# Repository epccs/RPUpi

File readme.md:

# RPUpi

From <https://github.com/epccs/RPUpi>

## Overview

Shield used to connect a Raspberry Pi Zero (or W) to serial that can be shared (multidrop). The targets presently available are [RPUno], [RPUlux], and [Irrigate7]. The hardware allows the bus to be controlled so the host sees a single target (for bootload) or any number of them.  

A [RPUadpt] shield is also available if the host SBC does not use the Raspberry Pi 40 pin header.

[RPUno]: https://github.com/epccs/RPUno
[RPUlux]: https://github.com/epccs/RPUlux
[Irrigate7]: https://github.com/epccs/Irrigate7
[RPUadpt]: https://github.com/epccs/RPUadpt
[RPUftdi]: https://github.com/epccs/RPUftdi

## Status

[Options](./Hardware#bill-of-materials)

## [Hardware](./Hardware)

Hardware files include schematic and board images, bill of materials, and my notes on testing, evaluation, and schooling.

## Example

Both the SBC and microcontroller(s) can run simple UART serial communication software (e.g. all the RS232 software I have tried seems to work). I prefer textual commands, so my examples generally use a textual command processor which echoes back the command like an interactive terminal, the commands are used by the firmware command processor to run routines or configure state machines on the bare metal microcontrollers. The SBC host the toolchain so it can compile the firmware from the source which can be managed with git (e.g. GitHub, GitLab...) or anyway the user wishes. The toolchains uploader can be used to send the firmware to the targets bootloader. The result is one or more bare metal targets can receive updates that are compiled from source without the need for a bare metal network stack. This is not an IoT system, it is a computer hosting an operating system and toolchain connected with physical wires to bare metal embedded controllers. It is also not dependent on any cloud-based services.

To bootload the AVR from the Raspberry Pi hardware serial port it needs to be enabled for [serial] so Linux can use the port, also the [RTS and CTS] pin functions should be enabled since nRTS is used to start the bootloader (in place of the nDTR trick used by an Arduino Uno). 

[serial]: ./Hardware/Testing/linux.md#serial
[RTS and CTS]: ./RPiRtsCts

The Pi Zero also needs a way to [halt] from a push button. When the RPUpi shield is mounted on a target board (e.g. [RPUno]) the VIN pin can be powered off with a [power management] technique.  This allows a manual shutdown and for the local target to request a halt using an I2C command. It should help with redundancy techniques, so two or more SBC's with [failover] can ensure data from the targets keep flowing. 

[failover]: https://en.wikipedia.org/wiki/Failover
[halt]: ./Shutdown
[power management]: https://github.com/epccs/RPUno/tree/master/PwrMgt

## AVR toolchain

The core files for this boards bus manager are in the /lib folder. Each example has its files and a Makefile in its own folder. The toolchain packages that I use are available on Ubuntu and Raspbian. 

```
sudo apt-get install git make gcc-avr binutils-avr gdb-avr avr-libc avrdude
git clone https://github.com/epccs/RPUpi
```

* [gcc-avr](https://packages.ubuntu.com/search?keywords=gcc-avr)
* [binutils-avr](https://packages.ubuntu.com/search?keywords=binutils-avr)
* [gdb-avr](https://packages.ubuntu.com/search?keywords=gdb-avr)
* [avr-libc](https://packages.ubuntu.com/search?keywords=avr-libc)
* [avrdude](https://packages.ubuntu.com/search?keywords=avrdude)

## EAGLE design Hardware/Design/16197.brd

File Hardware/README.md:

# Hardware

## Overview

This board connects a Pi Zero [W] to a multi-drop serial bus and a control board with a target (e.g. [RPUno], [RPUlux], [RPUicp], [Irrigate7]). 

[RPUno]: https://github.com/epccs/RPUno
[RPUlux]: https://github.com/epccs/RPUlux
[RPUicp]: https://github.com/epccs/RPUicp
[Irrigate7]: https://github.com/epccs/Irrigate7

## Inputs/Outputs/Functions

```
        Pi Zero power is from a 5V SMPS regulator powered by the Vin pin
        Pi Zero UART connects crossover style to the rpubus pairs
        rpubus pairs daisy-chain to other RPUpi or RPUadpt shields
        The UART's from multiple targets may connect to the rpubus pairs 
        An out of band management pair is used to control host to target (P2P) connection.
        SPI is available between SBC and the local target.
```

## Uses

```
        Raspberry Pi with a Raspian Linux instance is a compelling platform.
        Accessing the machine instance with SSH is prefered.
        Serving files with Samba is availalbe, but not prefered.
        The machine instance has a physical serial link (rpubus ) to the bare metal targets.
```

## Notice

```
        If the Pi Zero bootloads its local board (the one under the RPUpi) then 
        the VIN power from the local board must not turn off after a reset 
        (the defaut setup has been tested and works). 
 ```

# Table Of Contents

1. [Status](#status)
2. [Design](#design)
3. [Bill of Materials](#bill-of-materials)
4. [How To Use](#how-to-use)

# Status

```
        ^5  Done: Design, Layout, BOM, Review*, Order Boards, Assembly, Testing,
            WIP: Evaluation.
            Todo: 
            *during review the Design may change without changing the revision.
            AVR's nSS should goto R-Pi's nCE00 not nCE10.

        ^4  Done: Design, Layout, BOM, Review*, Order Boards, Assembly, Testing,
            WIP: Evaluation.
            Todo: 
            *during review the Design may change without changing the revision.
            IOREF is for I2C and UART
            SPI_IOREF is for SPI only
            Add SPI nSS so the Raspery Pi CE10 can use it, (it was tested with RPUadpt^6)
            remove ADC6 and ADC7.
            remove smd mounts for 100 Ohm pair termination.
            Use TI's 5V THVD1500, wich cost less and has better specs.
            Run Manager at 5V to match trancever's.
            Remove 3V3 regulator, which is no longer needed.
            Change Q1..Q3 to use K1N. 
```

Debugging and fixing problems i.e. [Schooling](./Schooling/)

Setup and methods used for [Evaluation](./Evaluation/)

# Design

The board is 0.063 thick, FR4, two layer, 1 oz copper with ENIG (gold) finish.

## Electrical Parameters (Typical)

```
        VIN pin needs 7V to 30V (RPUno has 12.8V) at up to 4W for SMPS regulator to power a Pi Zero
        5V pin needs 150mA (RPUno has 1+ Amp) to power RPU_BUS
```

## Mounting

```
        Shield or Mezzanine
```

## Electrical Schematic

## Testing

Check correct assembly and function with [Testing](./Testing/)

# Bill of Materials

The BOM is a CVS file, import it into a spreadsheet program like LibreOffice Calc (or Excel), or use a text editor.

Option | BOM's included
----- | ----- 
A. | [BRD] 
M. | [BRD] [SMD] [HDR] 
N. | [BRD] [SMD] [HDR] [POL]
Y. | [BRD] [SMD] [HDR] [POL] [CAT5]

[BRD]: ./Design/16197BRD,BOM.csv
[SMD]: ./Design/16197SMD,BOM.csv
[HDR]: ./Design/16197HDR,BOM.csv
[POL]: ./Design/16197POL,BOM.csv
[CAT5]: ./Design/16197CAT,BOM.csv

[Order Form](https://rpubus.org/Order_Form.html)

# How To Use

Your [Raspberry Pi] is your computer, you are the expert because I am not. Don't buy an RPUpi board and expect that I can help with your computer, I can not. So far I have found that SSH works and the AVR toolchain, so I am able to serial bootload the  ATmega328p, ATmega328pb, and ATmega1284p. I have tested SMBus and found it works but it does not do clock stretching, so let's not call it I2C. I have also tested SPI somewhat. The serial console program I use is picocom, the install package is built to do standard baud rates (e.g. 38.4k bps) so that is what I have been using (250kbps may work with other programs). 

[Raspberry Pi]: https://www.raspberrypi.org/forums/

## Simplified Serial

To allow a hardware UART on a Raspberry Pi Single Board Computer to interface with an AVR UART the following connections can be used. Notice that the AVR is powered by 3.3V.

Next, lets set things up to use an AVR at 5V. Using a buffer with IOFF for level shifting. Now I can turn off the SBC without locking (pulling down) the serial port lines (e.g. to the USB UART bridge).

## ICSP

[ArduinoISP] sketch on an Uno or the [ICSP] tool is what I use to program the bus manager with the [Remote] firmware. I then plug the RPUpi onto a target board and load my application firmware (e.g. target [RPUno] can run [i2c-debug]). The RPUpi's SBC host can communicate via serial with other target boards that have an RPUBUS. The additional boards will need the [Remote] firmware (on there manager) to have a different bus address.

[ArduinoISP]: https://github.com/arduino/Arduino/blob/master/build/shared/examples/11.ArduinoISP/ArduinoISP/ArduinoISP.ino
[ICSP]: https://github.com/epccs/Driver/tree/master/ICSP
[Remote]: https://github.com/epccs/RPUpi/tree/master/Remote
[i2c-debug]: https://github.com/epccs/RPUno/tree/master/i2c-debug

## Pi Zero Setup 

The Pi Zero is a Single Board Computer (SBC) running [Linux]. I use it as a network machine and to run a toolchain at the network edge. It has enough memory and processing power for the AVR toolchain (and others that I have not tested). It also does self-hosted compiling for (e.g. compiles programs to run on itself) and has lots of applications and services. My use is sort of like a headless test bench computer embedded next to the bare metal control boards, I daisy-chain the serial to each target I want to bootload. Is it IoT, no it is not, it is a classic control system (but it is headless), but I can interact with the target boards over an SSH session (e.g. in other words it does what IoT should). 

[Linux]: ./Testing/linux.md

The BCM2835 Broadcom chip used in the Raspberry Pi Zero is an ARM11 running at 1 GHz it has good support with the [Raspbian] distribution. 

[Raspbian]: https://www.raspbian.org/

## Serial

The Pi serial port (RX is BCM 15 and TX is BCM 14) is crossover connected at the transceivers that drive the differential pairs and then connect to the shield's target header for Tx and Rx e.g. BCM Rx goes through a transceiver to the target's Tx pin on the shield. This allows the SBC to talk to the shield's target with serial as is expected as well as being copied to the other transceivers connected to the differential pairs. 

The Pi's handshake lines nCTS and nRTS lines are on BCM 16 and 17 when the ALT3 option is active. BCM 17 is on the original 26 pin Pi connector, but BCM 16 is on the new 40 pin connector (e.g. use a 40 pin model). I use this [rpirtscts] program as a command-line utility for enabling hardware flow control on the Pi Zero serial port. 

[rpirtscts]: https://github.com/epccs/RPUpi/tree/master/RPiRtsCts

On the RPUpi board, the Pi Zero serial lines (Rx, Tx, nRTS, and nCTS) have been interfaced through a 74LVC07A buffer which is powered from the Pi's 3V3 power. When the Pi Zero is powered off the IOFF feature of the buffer will hi-z the output (it's an open collector output) which will allow a pull-up to set the proper value on nRTS and the Tx line. This allows the RPUBUS to be used when the Pi Zero is powered off (or not plugged in). Also, a 74LVC07A buffer is used between the transceiver and the controller that the shield is pluged into so it can run at 3.3V or 5V, this buffer is powered from the controller so it works without the SBC.

When the Pi's handshake lines are enabled the nRTS line is used to start a targets bootloader. When avrdude opens the serial port the nRTS goes active, that is it pulls low the bus manager sees this and broadcast a bootload address on the DTR pair causing everything but the bootload device which is also reset to lockout and thus avrdude sees a single target running its serial bootloader. Since picocom does the same thing I have to make sure the target is one I want to reset, and then have to wait for that targets bootloader to timeout and its application to get the bus address from its shield. 

## Full Duplex Serial Management

The shield has a manager that can enable each transceiver's receiver and driver so that the targets can be isolated or connected from the serial bus; the implications are significant. The original intent was to allow boot loading with a point to point full duplex mode (e.g., target with optiboot/xboot and the host running avrdude). It supports boot loading a new executable binary image over a severely goofed up bare metal application; I have tried to retain the nearly bulletproof upload found with RS232 using optiboot and avrdude.

## Transceiver (RS-485)

The transceivers used have a built-in fail-safe bias, which is a little complicated to explain, but it makes an undriven bus (e.g., 0V is the failed condition) a defined logic state (HIGH). That is if I turn off the transceiver driving the bus (only one should steer the bus at any time), it is guaranteed to be in a defined state (e.g., HIGH). I have set up the transceivers to automatically turn off the driver while the UART output is HIGH (its default value). That means the driver will automatically drive the bus only when data is sent, so nothing needs to be done in software to turn on or off the transceivers. The bus manager may override.

## SPI

The SBC's SPI lines (MOSI, SCK, MISO, ^4 adds nSS) are interfaced through a 74LVC07A buffer. The lines MOSI, SCK, and nSS are powered from the SBC 3V3 power. When the SBC is powered off the IOFF feature of the buffer will hi-z its open collector output which will allow a pull-up to set the value on SCK and the MOSI line or allow the MCU to control them. 

Known issues: RPUno has its SPI lines run to user connectors for digital control so make sure those are free if SPI is to be used.

## I2C

The SBC has an SMBus port when it is running Linux. The Raspberry Pi Zero has 1.8k pull-ups to 3.3V, and when it is powered down those resistors pull the I2C lines and lock the bus. That is why the ^4 manager has an ATmega328pb. The second I2C port can talk to the SBC with SMBus commands, and the original I2C port can talk to the target.

## SD

SBC SD Card [corruption] can happen when the SD card is doing wear leveling operations at the time power is removed. It is possible with this setup to push the shutdown button and have that run a [Shutdown] script. Also, the local programmable controller can initiate a power down with [PwrMgt] which monitors power before killing power to the shield (VIN pin). The idea is that wear leveling will draw current somewhat randomly until all the page updates are done. The BCM2835 will be halted, and looping (it is checking one of the I2C pins) and using a steady current draw. So when the current draw is stable, the wear leveling should be done and safe to disconnect the shield VIN.

[Shutdown]: https://github.com/epccs/RPUpi/tree/master/Shutdown
[PwrMgt]: https://github.com/epccs/RPUno/tree/master/PwrMgt
[corruption]: https://hackaday.com/2016/08/03/single-board-revolution-preventing-flash-memory-corruption/

## Security

Do not bootload bare metal over links that can have adversaries in the middle.

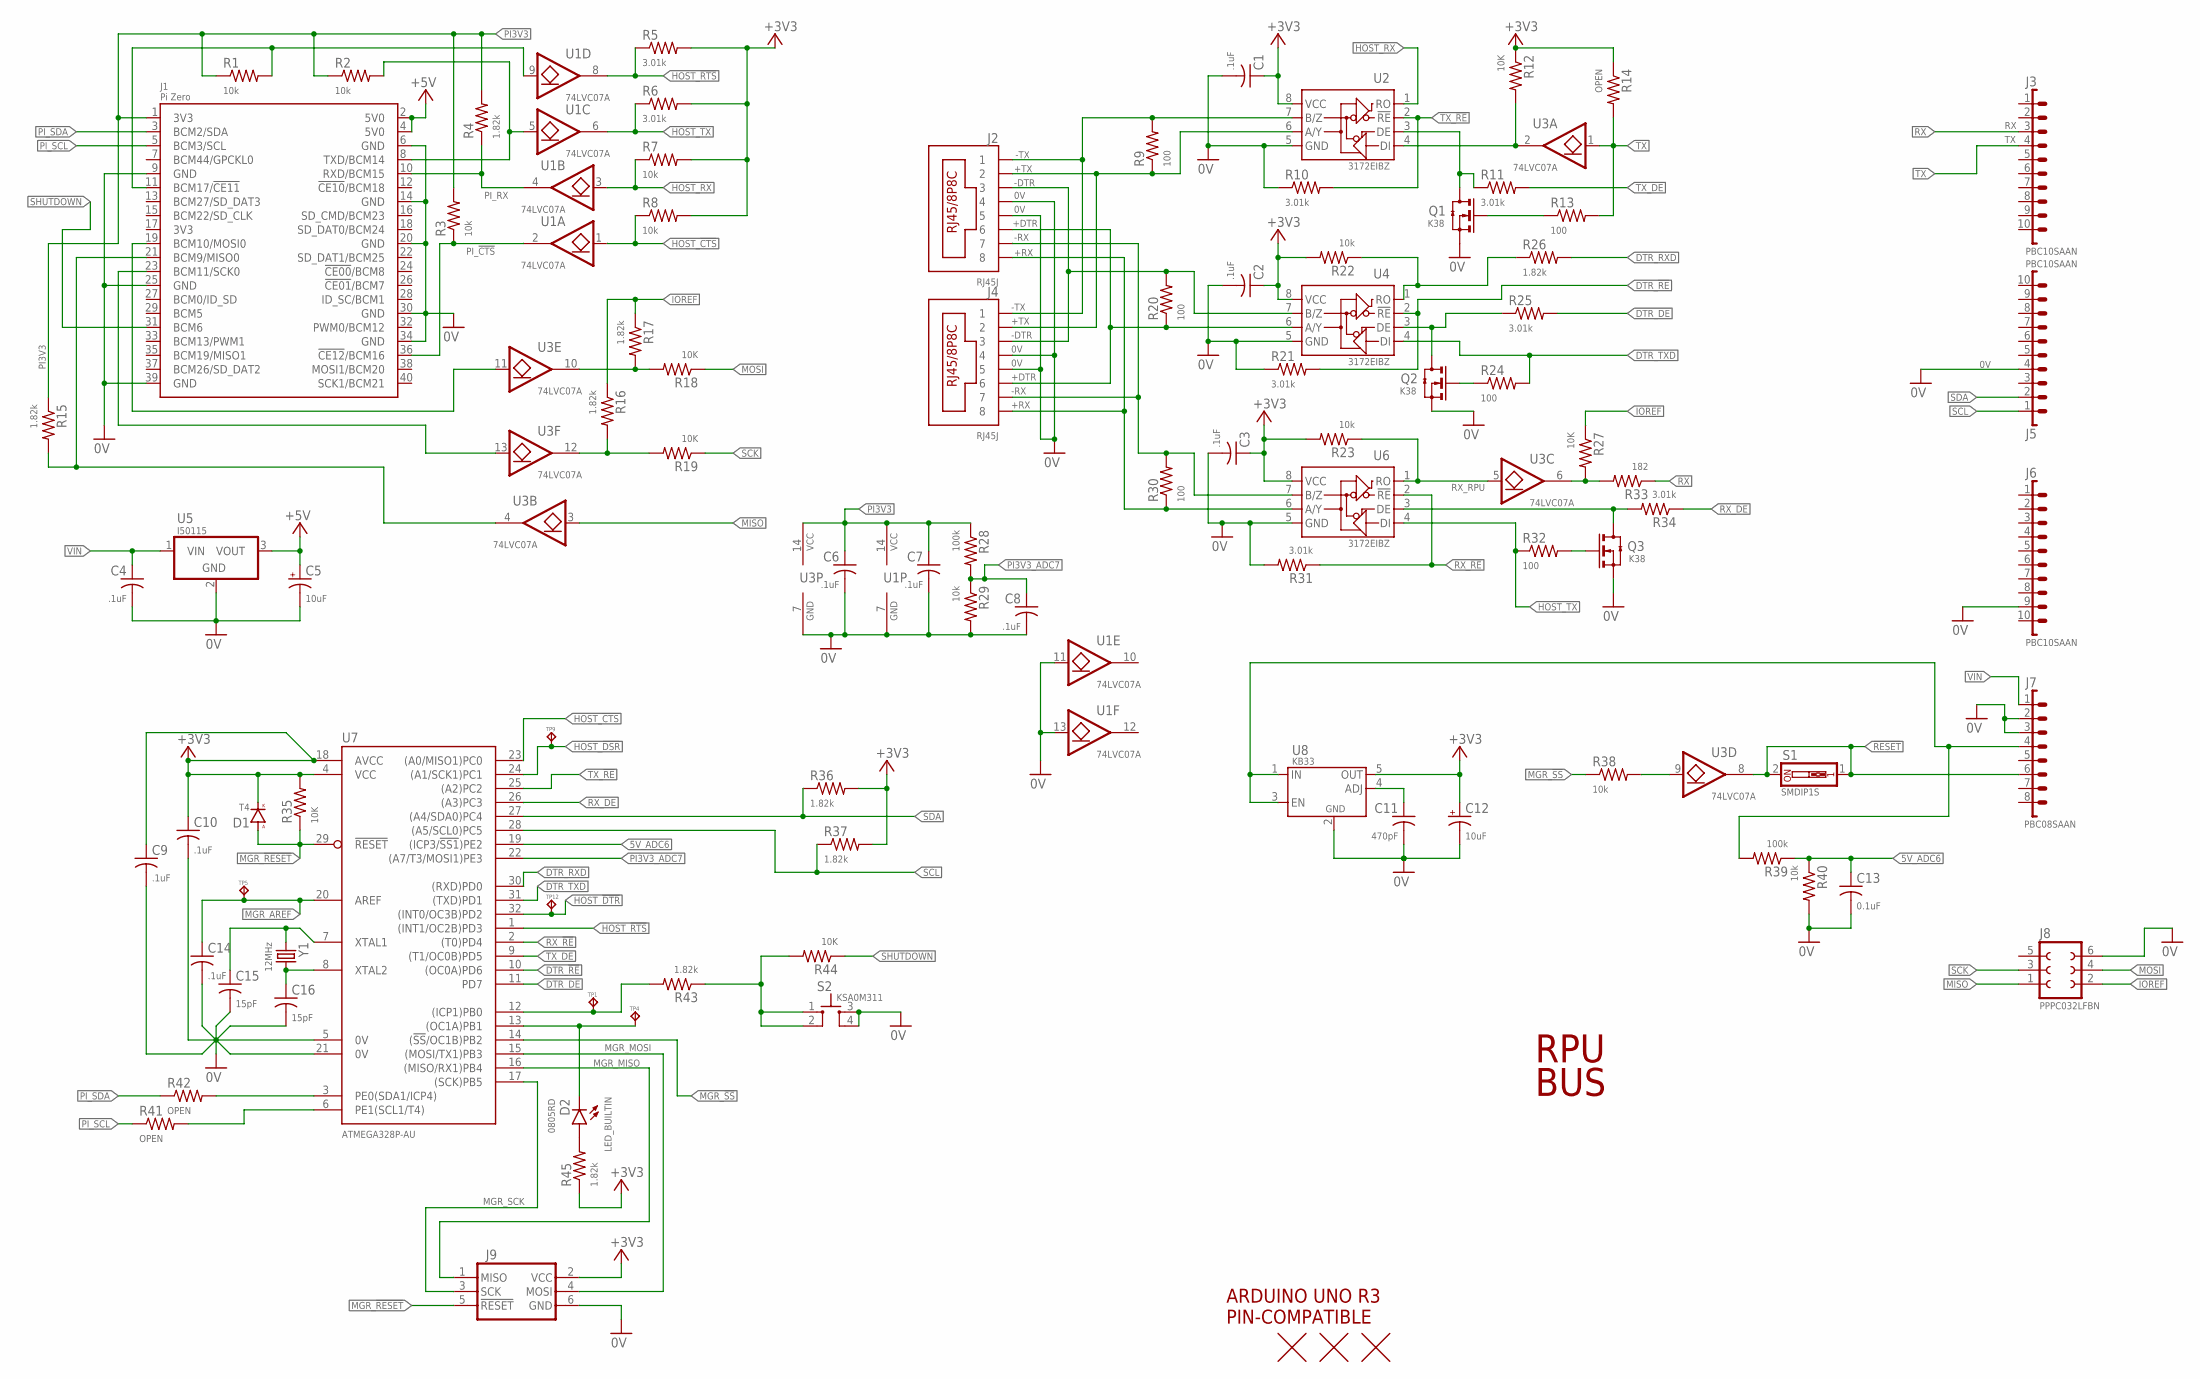
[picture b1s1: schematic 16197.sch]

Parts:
C1, C2, C3, C4, C6, C7, C8, C9, C10, C14: .1uF; C0603(1608)
C5, C12: 10uF; 3216
C11: 470pF; C0603(1608)
C13: 0.1uF; C0603(1608)
C15, C16: 15pF; C0603(1608)
D1: T4; SOD123
D2: 0805RD; C0805(2012)
J1: Pi Zero; RASPI_ZERO_V40PIN
J2, J4: RJ45J; RJ45-8HZT
J3, J5, J6: PBC10SAAN; 1X10
J7: PBC08SAAN; 1X8
J8: PPPC032LFBN; F2X3
J9: ISP-SPIPTH; ISP
Q1, Q2, Q3: K38; SOT23
R1, R2, R3, R7, R8, R22, R23, R29, R38, R40: 10k; C0805(2012)
R4, R15, R16, R17, R26, R36, R37, R43, R45: 1.82k; C0805(2012)
R5, R6, R10, R11, R21, R25, R31, R34: 3.01k; C0805(2012)
R9, R13, R20, R24, R30, R32: 100; C0805(2012)
R12, R18, R19, R27, R35, R44: 10K; C0805(2012)
R14, R41, R42: OPEN; C0805(2012)
R28, R39: 100k; C0805(2012)
R33: 182; C0805(2012)
S1: SMDIP1S; SMD-DIPSWITCH-1
S2: KSA0M311; 0M311
TP1, TP4, TP5, TP9, TP12: TPPAD1-08; P1-08
U1, U3: 74LVC07A; 14SOIC
U2, U4, U6: 3172EIBZ; SOIC8
U5: I50115; OKI-78SR-H
U7: ATMEGA328P-AU; TQFP32-08
U8: KB33; SOT23-5,SOT25
U$1: ARDUINO-UNO; ARDUINO_UNO
U$2, U$3, U$4: FIDUCIAL1.27; FIDUCIAL-1.27
Y1: 12MHz; CSM-3X

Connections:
0V: C1.2, C2.2, C3.2, C4.2, C5.-, C6.2, C7.2, C8.2, C9.2, C10.2, C11.2, C12.-, C13.2, C14.2, C15.2, C16.2, J1.6 (GND), J1.9 (GND), J1.14 (GND), J1.20 (GND), J1.25 (GND), J1.30 (GND), J1.34 (GND), J1.39 (GND), J2.4, J2.5, J4.4, J4.5, J5.4, J6.9, J7.2, J7.3, J8.6, J9.6 (GND), Q1.2(S) (S), Q2.2(S) (S), Q3.2(S) (S), R10.1, R21.1, R29.2, R31.2, R40.2, S2.3, S2.4, U1.7 (GND), U1.11 (I), U1.13 (I), U2.5 (GND), U3.7 (GND), U4.5 (GND), U5.2 (GND), U6.5 (GND), U7.5 (0V), U7.21 (0V), U8.2 (GND)
5V_ADC6: C13.1, R39.1, R40.1, U7.19 ((ICP3/!SS1!)PE2)
!RESET: J7.6, S1.1, S1.2, U3.8 (O)
+3V3: C1.1, C2.1, C3.1, C9.1, C10.1, C12.+, D1.C (K), J9.2 (VCC), R5.2, R6.2, R7.2, R8.2, R12.1, R14.1, R22.2, R23.2, R35.2, R36.2, R37.2, R45.1, U2.8 (VCC), U4.8 (VCC), U6.8 (VCC), U7.4 (VCC), U7.18 (AVCC), U8.5 (OUT)
+5V: C5.+, J1.2 (5V0), J1.4 (5V0), U5.3 (VOUT)
+DTR: J2.6, J4.6, R20.1, U4.6 (A/Y)
+RX: J2.8, J4.8, R30.1, U6.6 (A/Y)
+TX: J2.2, J4.2, R9.1, U2.6 (A/Y)
-DTR: J2.3, J4.3, R20.2, U4.7 (B/Z)
-RX: J2.7, J4.7, R30.2, U6.7 (B/Z)
-TX: J2.1, J4.1, R9.2, U2.7 (B/Z)
DTR_!RE: R21.2, U4.2 (!RE), U7.10 ((OC0A)PD6)
DTR_DE: R25.2, U7.11 (PD7)
DTR_RXD: R26.2, U7.30 ((RXD)PD0)
DTR_TXD: R24.2, U4.4 (DI), U7.31 ((TXD)PD1)
HOST_!CTS: R8.1, U1.1 (I), U7.23 ((A0/MISO1)PC0)
HOST_!DSR: TP9.TP, U7.24 ((A1/SCK1)PC1)
HOST_!DTR: TP12.TP, U7.32 ((INT0/OC3B)PD2)
HOST_!RTS: R5.1, U1.8 (O), U7.1 ((INT1/OC2B)PD3)
HOST_MISO: J1.21 (BCM9/MISO0), R15.2, U3.4 (O)
HOST_MOSI: J1.19 (BCM10/MOSI0), U3.11 (I)
HOST_RX: R7.1, U1.3 (I), U2.1 (RO)
HOST_SCK: J1.23 (BCM11/SCK0), U3.13 (I)
HOST_TX: R6.1, R32.1, U1.6 (O), U6.4 (DI)
ICP1: R43.2, TP1.TP, U7.12 ((ICP1)PB0)
IOREF: J8.2, R16.1, R17.1, R27.1
LED_BUILTIN: D2.K, TP4.TP, U7.13 ((OC1A)PB1)
MGR_!RESET: D1.A, J9.5 (!RESET), R35.1, U7.29 (!RESET)
MGR_!SS!: R38.1, U7.14 ((!SS!/OC1B)PB2)
MGR_AREF: C14.1, TP5.TP, U7.20 (AREF)
MGR_MISO: J9.1 (MISO), U7.16 ((MISO/RX1)PB4)
MGR_MOSI: J9.4 (MOSI), U7.15 ((MOSI/TX1)PB3)
MGR_SCK: J9.3 (SCK), U7.17 ((SCK)PB5)
MISO: J8.1, U3.3 (I)
MOSI: J8.4, R18.1
unnamed: J1.8 (TXD/BCM14), R2.2, U1.5 (I)
unnamed: R38.2, U3.9 (I)
unnamed: J1.11 (BCM17/!CE11!), R1.2, U1.9 (I)
unnamed: R16.2, R19.2, U3.12 (O)
unnamed: R17.2, R18.2, U3.10 (O)
unnamed: R43.1, R44.2, S2.1, S2.2
unnamed: R27.2, R33.2, U3.6 (O)
unnamed: Q3.3(D) (D), R34.2, U6.3 (DE)
unnamed: Q1.1(G) (G), R13.1
unnamed: Q1.3(D) (D), R11.1, U2.3 (DE)
unnamed: R22.1, R26.1, U4.1 (RO)
unnamed: Q2.3(D) (D), R25.1, U4.3 (DE)
unnamed: Q2.1(G) (G), R24.1
unnamed: C11.1, U8.4 (ADJ)
unnamed: Q3.1(G) (G), R32.2
unnamed: D2.A, R45.2
NODE5V: J7.4, R39.2, U8.1 (IN), U8.3 (EN)
PI3V3: C6.1, C7.1, J1.1 (3V3), R1.1, R2.1, R3.2, R4.2, R15.1, R28.1, U1.14 (VCC), U3.14 (VCC)
PI3V3_ADC7: C8.1, R28.2, R29.1, U7.22 ((A7/T3/MOSI1)PE3)
PI_!CTS: J1.36 (!CE12!/BCM16), R3.1, U1.2 (O)
PI_RX: J1.10 (RXD/BCM15), R4.1, U1.4 (O)
PI_SCL: J1.5 (BCM3/SCL), R41.1
PI_SDA: J1.3 (BCM2/SDA), R42.1
RX: J3.3, R33.1
RX_!RE: R31.1, U6.2 (!RE), U7.2 ((T0)PD4)
RX_DE: R34.1, U7.26 ((A3)PC3)
RX_RPU: R23.1, U3.5 (I), U6.1 (RO)
SCK: J8.3, R19.1
SCL: J5.1, R37.1, U7.28 ((A5/SCL0)PC5)
SCL1: R41.2, U7.6 (PE1(SCL1/T4))
SDA: J5.2, R36.1, U7.27 ((A4/SDA0)PC4)
SDA1: R42.2, U7.3 (PE0(SDA1/ICP4))
SHUTDOWN: J1.31 (BCM6), R44.1
TX: J3.4, R13.2, R14.2, U3.1 (I)
TX_!RE: R10.2, U2.2 (!RE), U7.25 ((A2)PC2)
TX_DE: R11.2, U7.9 ((T1/OC0B)PD5)
TX_RPU: R12.2, U2.4 (DI), U3.2 (O)
VIN: C4.1, J7.1, U5.1 (VIN)
XTAL1: C15.1, U7.7 (XTAL1), Y1.1
XTAL2: C16.1, U7.8 (XTAL2), Y1.2

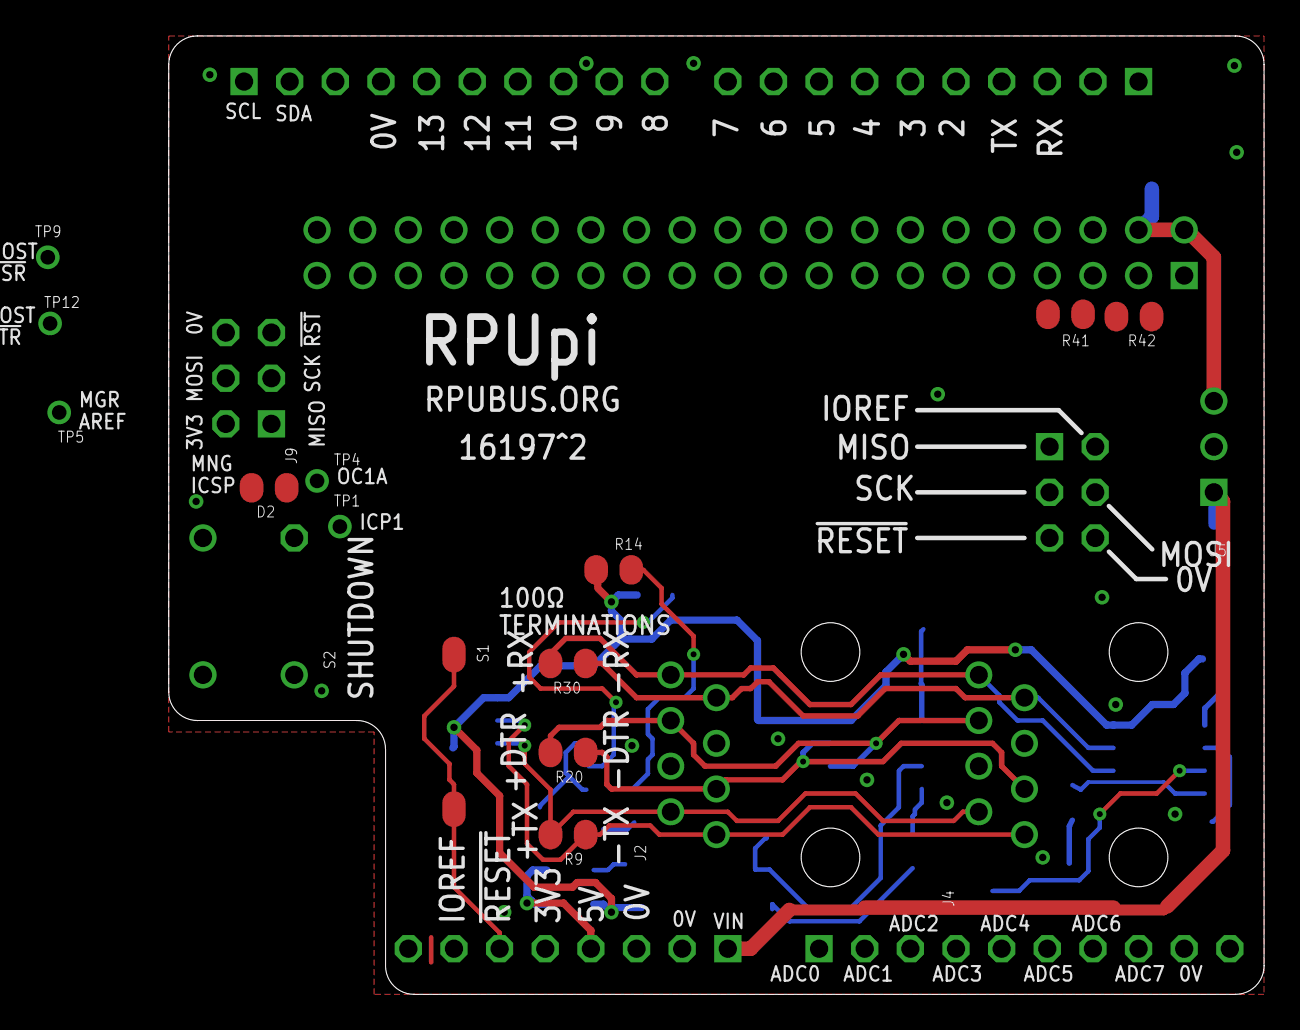
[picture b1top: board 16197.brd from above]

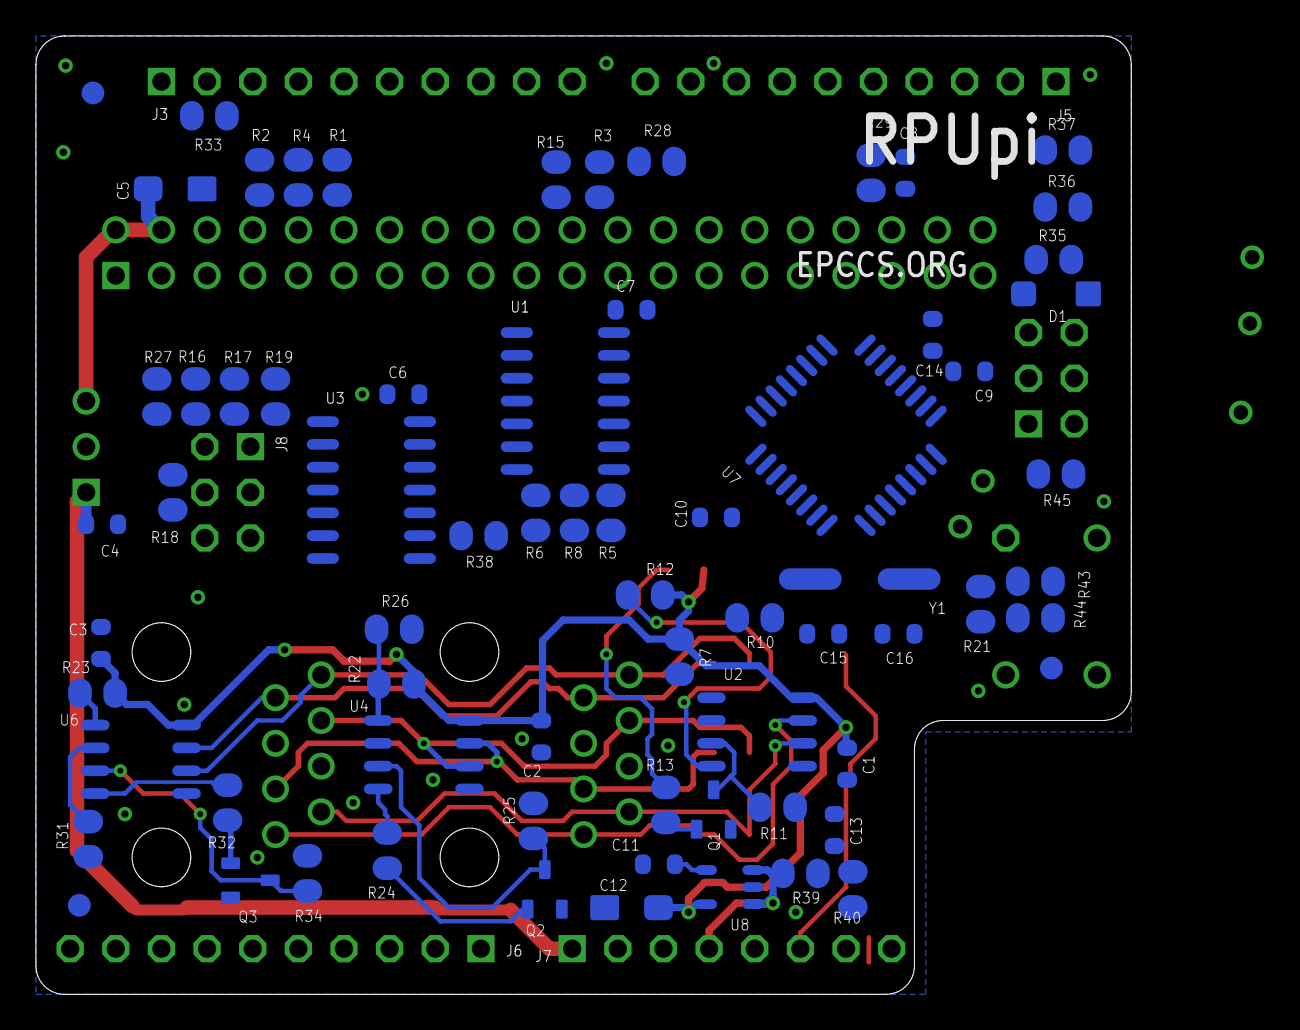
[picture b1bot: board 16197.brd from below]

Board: 2 copper layers, 61.0 x 53.3 mm, 95 parts (75 on the bottom side), 75 nets.

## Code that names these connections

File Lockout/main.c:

/* RPUpi Lockout
 * Copyright (C) 2016 Ronald Sutherland
 *
 * This Library is free software: you can redistribute it and/or modify
 * it under the terms of the GNU General Public License as published by
 * the Free Software Foundation, either version 3 of the License, or
 * (at your option) any later version.
 *
 * This Library is distributed in the hope that it will be useful,
 * but WITHOUT ANY WARRANTY; without even the implied warranty of
 * MERCHANTABILITY or FITNESS FOR A PARTICULAR PURPOSE.  See the
 * GNU General Public License for more details.
 *
 * You should have received a copy of the GNU General Public License 
 * along with the Arduino DigitalIO Library.  If not, see
 * <http://www.gnu.org/licenses/>.
 */ 

#include <util/delay.h>
#include <avr/io.h>
#include "../lib/timers.h"
#include "../lib/pin_num.h"
#include "../lib/pins_board.h"

#define BLINK_DELAY_OFF 900UL
#define BLINK_DELAY_ON 100UL

static unsigned long blink_at;
volatile uint8_t shutdown_status;

// non-blocking blink (e.g.  _delay_ms(1000) is blocking delay)
void blink_on_active(void)
{
    unsigned long kRuntime = millis() - blink_at;
    
    if ((!shutdown_status) && digitalRead(LED_BUILTIN) && (kRuntime > BLINK_DELAY_OFF) ) 
    {
        digitalWrite(LED_BUILTIN, LOW);
        blink_at += BLINK_DELAY_OFF;
    }
    else if ((!shutdown_status) && (!digitalRead(LED_BUILTIN)) && (kRuntime > BLINK_DELAY_ON) ) 
    {
        digitalWrite(LED_BUILTIN, HIGH);
        blink_at += BLINK_DELAY_ON;
    }
}

int main(void)
{
    pinMode(LED_BUILTIN, OUTPUT);
    digitalWrite(LED_BUILTIN, HIGH);
    
    // setup RTS/CTS so the host can send
    pinMode(HOST_nRTS, INPUT);
    digitalWrite(HOST_nRTS, HIGH); // with AVR when the pin DDR is set as an input setting pin high will trun on a weak pullup 
    pinMode(HOST_nCTS, OUTPUT);
    digitalWrite(HOST_nCTS, LOW);
    
    // setup DTR/DSR, they are just test points on RPUpi
    pinMode(HOST_nDTR, INPUT);
    digitalWrite(HOST_nDTR, HIGH); // another weak pullup 
    pinMode(HOST_nDSR, OUTPUT);
    digitalWrite(HOST_nDSR, LOW);

    // setup DTR transceiver
    pinMode(DTR_TXD, OUTPUT);
    digitalWrite(DTR_TXD, LOW);
    pinMode(DTR_DE, OUTPUT);
    digitalWrite(DTR_DE, LOW);  // yep there is startup glitch, so disallow DTR pair driver until after the UART is running.
    pinMode(DTR_nRE, OUTPUT);
    digitalWrite(DTR_nRE, LOW);

    // setup TX and RX transceiver so both the host and node are locked out from the differential pairs 
    pinMode(RX_DE, OUTPUT);
    digitalWrite(RX_DE, LOW);  // disallow RX pair driver to enable if FTDI_TX is low
    pinMode(RX_nRE, OUTPUT);
    digitalWrite(RX_nRE, HIGH);  // disable RX pair recevior to output to local MCU's RX input
    pinMode(TX_DE, OUTPUT);
    digitalWrite(TX_DE, LOW); // disallow TX pair driver to enable if TX (from MCU) is low
    pinMode(TX_nRE, OUTPUT);
    digitalWrite(TX_nRE, HIGH);  // disable TX pair recevior to output to FTDI_RX input

    // this firmware allows the Pi Zero Serial to be used as a command line interface (e.g. its default setup).
    pinMode(nSS, OUTPUT); // nSS is connected to a open collector buffer that can pull the node's MCU nRESET low
    digitalWrite(nSS, LOW); // hold the node in RESET
    pinMode(SHUTDOWN, INPUT);
    digitalWrite(SHUTDOWN, HIGH); // with AVR when the pin DDR is set as an input setting pin high will trun on a weak pullup 
    
    shutdown_status = 0;
    
    initTimers(); //Timer0 Fast PWM mode, Timer1 & Timer2 Phase Correct PWM mode.

    sei(); // Enable global interrupts to start TIMER0

    // the UART has a startup glitch... this should keep it from to the DTR pair.
    // NOTE UART is not initalized for this program, but will keep the logic.
    _delay_ms(10);
    digitalWrite(DTR_DE, HIGH); 

    while (1) 
    {
        blink_on_active();
        
        uint8_t shutdown_now = ! digitalRead(SHUTDOWN);
        
        if (!shutdown_status && shutdown_now)
        {
            shutdown_status = 1;
            digitalWrite(LED_BUILTIN, HIGH);
        }
    }    
}

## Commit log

2016-10-11 :lollipop: Added .gitattributes
2016-10-11 init
2016-10-12 Lockout: with shutdown pin and a non-blocking blink
2016-10-12 Shutdown: python script to halt when sw on BCM6 is pressed
2016-10-12 RPiRtsCts: tool used to enable RTS/CTS flow control
2016-10-13 CheckDTR: test for DTR transceiver
2016-10-14 CheckDTR: use the shutdown switch to remove RX/TX lockout
2016-11-16 Hardware: add
2016-12-19 Hardware: moving more to Github
2016-12-20 Hardware: md linking
2016-12-21 Hardware: assy ^1 done, issue with i2c found and the workaround
2016-12-22 Hardware: evaluate mounting
2016-12-28 Hardware: testing ^1 done, add tx pull up, next is evaluation.
2016-12-29 Hardware: ^1 add 10k on sck and mosi
2017-01-24 Hardware: note problem with serial at power down
2017-01-24 example is a little more refined
2017-01-27 notes on bootloading AVR from Pi serial port
2017-02-08 Hardware: ^2 dsgn in wip
2017-04-12 Hardware: ^2 review
    will move away from eagle, so not going to include
2017-04-12 Hardware: no silver bullet for type-o
2017-04-13 Hardware: ^2 bom up to date
2017-04-13 Hardware: 100 ohm termination not placed
2017-04-19 status
2017-04-28 Hardware: planes done with 8 mil to fill between IDE conn better
2017-04-30 Hardware: ^2 on order
2017-05-10 Hardware: change bom to comma separated values
2017-05-14 Hardware: ^2 assembly
2017-05-20 Hardware: ^2 testing is wip
2017-05-26 Remote: add this firmware from RPUadpt
2017-05-26 Hardware: node names are used as macro names and must be C identifiers
2017-05-26 Hardware: another diagram
2017-05-27 Hardware: problem, U3 does not have power so serial from shild is blocked
2017-07-02 Hardware: ^3 on order
2017-07-30 Hardware: ^3 assembly done
2017-08-11 Hardware: ^3 testing done, omg it bootloads once cts/rts is enabled.
2017-08-12 Hardware: refine linux setup
2017-08-13 Hardware: ^3 bootload evaluation
2017-08-14 Remote: document sneaky mode which it is doing now (more or less) at power up
2017-08-15 Hardware: detect BOOT_PORT with makefile for controller board firmware
2017-08-24 Hardware: ^3 build with new parts and test spi
2017-09-02 add link to tindie
2017-10-01 Hardware: link linux wireless cli setup for r-pi
2017-10-28 Hardware: did not know that rpi-update was for firmware
2018-01-12 Hardware: doc of a simplified serial between Pi and AVR
2018-01-12 Hardware: add gnd to simple serial view
2018-01-13 Hardware: remove weak pull-up from simple serial view
2018-01-14 Hardware: add more info on pi2avr simple serial
2018-01-17 Hardware: add more info on simple serial, pi2avr with ioff
2018-01-18 Hardware: simple serial, pi2avr with ioff at 16MHz
2018-01-30 Hardware: notes for VSC
2018-03-06 Hardware: update raspbian to stretch (clean, don't upgrade from jessie)
2018-03-29 Remote: readme show i2c-debug^1 commands, also how to enable Pi zero as a host
2018-05-28 Hardware: linux setup notes
2018-05-28 Hardware: linux wifi ssid case
2018-06-20 flags changed for avrdude upgrade
2018-06-28 Hardware: notes
2018-07-13 https
2018-09-16 Hardware: ^4 schmatic design
2018-09-20 Hardware: ^4 layout, bom is next
2018-09-22 Hardware: ^4 bom, review is next
2018-09-23 Hardware: ^4 reviewing
2018-10-01 WSGIdaemon: init it needs work
2018-10-02 WSGIdaemon: add arguments and deal with bad request
2018-10-03 WSGIdaemon: browser is saying No 'Access-Control-Allow-Origin' header
2018-10-10 WSGIdaemon: at proof of concept stage
2018-10-11 WSGIdaemon: allow_origin from anywhere
2018-10-12 WSGIdaemon: do a list of commands with the client
2018-10-15 WSGIdaemon: chk cmd echo, chk json rply, only use json for http response
2018-10-15 WSGIdaemon: client parse's json from avr and fills dom elements
2018-10-17 WSGIdaemon: clients seem to like the json, add cpyrht
2018-10-31 Hardware: ^4 reviewing+ 485tx_en worked thus swap K38 for K1N
2019-01-20 WSGIdaemon: local network, look at K7..K5 on an irrigate7
2019-02-15 Hardware: ^4 assembly done
2019-02-21 BlinkLED: copy from RPUadpt and add 328pb files from atpack 1.3.300
2019-02-22 CheckDTR: 328pb update, note F_CPU and BAUD not used
2019-02-24 Remote: on ^4 the 328pb has i2c1 to use with r-pi smbus
2019-02-28 Hardware: ^ testing done starting evaluation
2019-03-01 Hardware: ^4 evaluation of smbus
2019-03-02 Hardware: ^5 design is wip
2019-03-02 Hardware: ^5 reviewing
2019-04-24 licences LGPL in lib files and GPL in the app files
2019-04-27 Remote: refactor bus manager state so it can be used outside main
2019-04-28 Remote: refactor i2c and smbus commands
2019-04-28 Remote: normal mode setup funciton moved
2019-04-28 Remote: bootload and lockout mode setup funciton moved
2019-05-13 Remote: use i2c command as index of function pointer array
2019-05-20 Remote: use i2c commmands for smbus commands, smbus buffer works same as past
2019-05-21 Remote: add arduino_mode
2019-06-02 Remote: refactor id in eeprom
2019-06-03 WSGIdaemon: notes from forum
2019-06-03 uart glitch at init, optiboot does not glitch so do what it does.
2019-06-03 Remote: simple main, uart should be glitch free at init
2019-06-04 Remote: test_mode wip
2019-06-08 Remote: found uart was not glitch free, when testing p2p mode
2019-06-11 Remote: test_mode wip, having issue with i2c command echo
2019-06-13 Remote: smbus confusion
2019-06-15 Remote: smbus still not woking with r-pi-zero
2019-06-17 Remote: #1 twi core buffer interleaving used to limit clock-stretching
2019-06-18 Remote: glitch on DTR pair, so split out functions to think about them.
    also working on transceiver test mode
2019-06-21 Remote: add a check byte for use with DTR pair and do some evaluation
2019-07-05 Remote: shutdown, manual works more like i2c cmd
2019-07-06 Remote: add rts and cts cntl to test mode bits 7 and 6 so they can be checked
2019-07-09 Remote: add dtr pair load when transceiver enabled durring testmode
2019-07-10 Hardware: testing ^5 done, next is evaluation
2019-07-11 Hardware: use 100 ohm on both ends of rpubus for evaluation
2019-07-16 Remote: used this to init gravimetric manager.
    also tested vscode remote.
2019-09-28 notes
2020-05-03 linux notes

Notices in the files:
parts and their libraries:
P-DCDC: Copyright (C) 2013 Ronald Steven Sutherland
under the terms of the GNU Free Documentation License, Version 1.2 or
any later version published by the Free Software Foundation; with no
C-C: Released under the Creative Commons
Attribution Share-Alike 3.0 License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
